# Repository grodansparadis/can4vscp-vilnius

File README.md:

# Vilnius A/D module

This module is part of the [VSCP project](https://www.vscp.org).  It is free to use, modify and sell. The only thing we kindly ask is that improvements and extensions are contributed back to the project (at your will). This to make the project better for everyone. All design files is licensed under the [MIT license](https://en.wikipedia.org/wiki/MIT_License).

## Abstraction

Vilnius A/D module is a CAN4VSCP based module that have four 10-bit A/D channels for 0-5V or 0-10V and also have two 5V I/O channels that can be set as inputs or outputs. General use is to read analog values and as all other VSCP modules you can get the readings reported automatically with a user specified period.

It is also possible to report A/D readings as a VSCP measurement linearized as a floating point value from the formula

measurement = k * A/D-value + m

where k and m are configurable 32-bit floating point constants. You have full control of which event is sent and which unit is used.

This means you can send out any A/D reading as a real unit such as voltage, temperature or in any other SI specified unit.

You can also assign alarm limits so that alarm events are sent when the level goes above a certain value or below a certain value.

Two I/O channels are available. Both can individually be set as inputs or outputs. ON/OFF or TurnOn/TurnOff events can be sent out when I/O change state.

The module can be attached to a standard DIN Rail or be mounted directly on a wall. The mounting enclosures are ordered as separate options when the module is ordered.

The module fully adopts to the VSCP CAN4VSCP specification and can be powered directly over the bus cable with a good 9-28V DC power source. This means there is no need for a separate power cable. VSCP CAN modules are designed to work on a VSCP4CAN bus which use ordinary RJ-45 connectors or use the daisy chain pinhead which can be used to connect modules that are mounted close to each other. For the bus a CAT5 or better twisted pair cable is used. Bus length can have a total length of 500 meters with drops of maximum 24 meters length (up to a total of 120 meters). As for all VSCP4CAN modules the communication speed is fixed at 125 kbps.

All VSCP modules contains information of there own setup, manual, hardware version, manufacturer etc. When VSCP modules are started up they have a default functionality that often is all that is needed to get a working setup. If the module have something to report it will send you an event and if it is setup to react on a certain type of event it will do it's work when you send event(s) to it. It does not need to be harder than that. 

---

## Project files

### User manual
  * [User Manual](https://grodansparadis.github.io/can4vscp-vilnius/#)

### Schematic, PCB, 3D files etc
  * [Schematics reversion B part 1](https://raw.githubusercontent.com/grodansparadis/can4vscp-vilnius/refs/heads/master/eagle/vilnius_sch1_rev_B.png), [part 2](https://raw.githubusercontent.com/grodansparadis/can4vscp-vilnius/refs/heads/master/eagle/vilnius_sch2_rev_B.png)
 * Hardware design files is made in [KiCad](https://kicad.org) and can be found in the `kicad` directory. Valid from reversion B of the hardware.
 * Gerber files for PCB production can be found in the `gerber` directory (in the `kicad` folder).
 * Eagle schema and board files for reversion A and B can be found in the `eagle` directory. They are no longer actively updated.

 ### Firmware

 The firmware is developed in [MPLAB X IDE](https://www.microchip.com/mplab/mplab-x-ide) using the [XC8 compiler](https://www.microchip.com/mplab/compilers).

  * Binary release files is available [here](https://github.com/grodansparadis/can4vscp-vilnius/releases)

### MDF - Module Description File(s)
  * [MDF file version: 10 Release date: 2024-04-25](http://www.eurosource.se/vilnius_1.xml)

### Support
If you need support, please open an issue in the [GitHub repository](https://github.com/grodansparadis/can4vscp-vilnius/issues).

### Buy a ready made modules
You can buy a ready made module from [Grodans Paradis](http://www.grodansparadis.com).

### Project related links
  * [VSCP project](https://www.vscp.org)
  * [VSCP Documentation site](https://docs.vscp.org/)
  * [VSCP Wiki](https://github.com/grodansparadis/vscp/wiki)

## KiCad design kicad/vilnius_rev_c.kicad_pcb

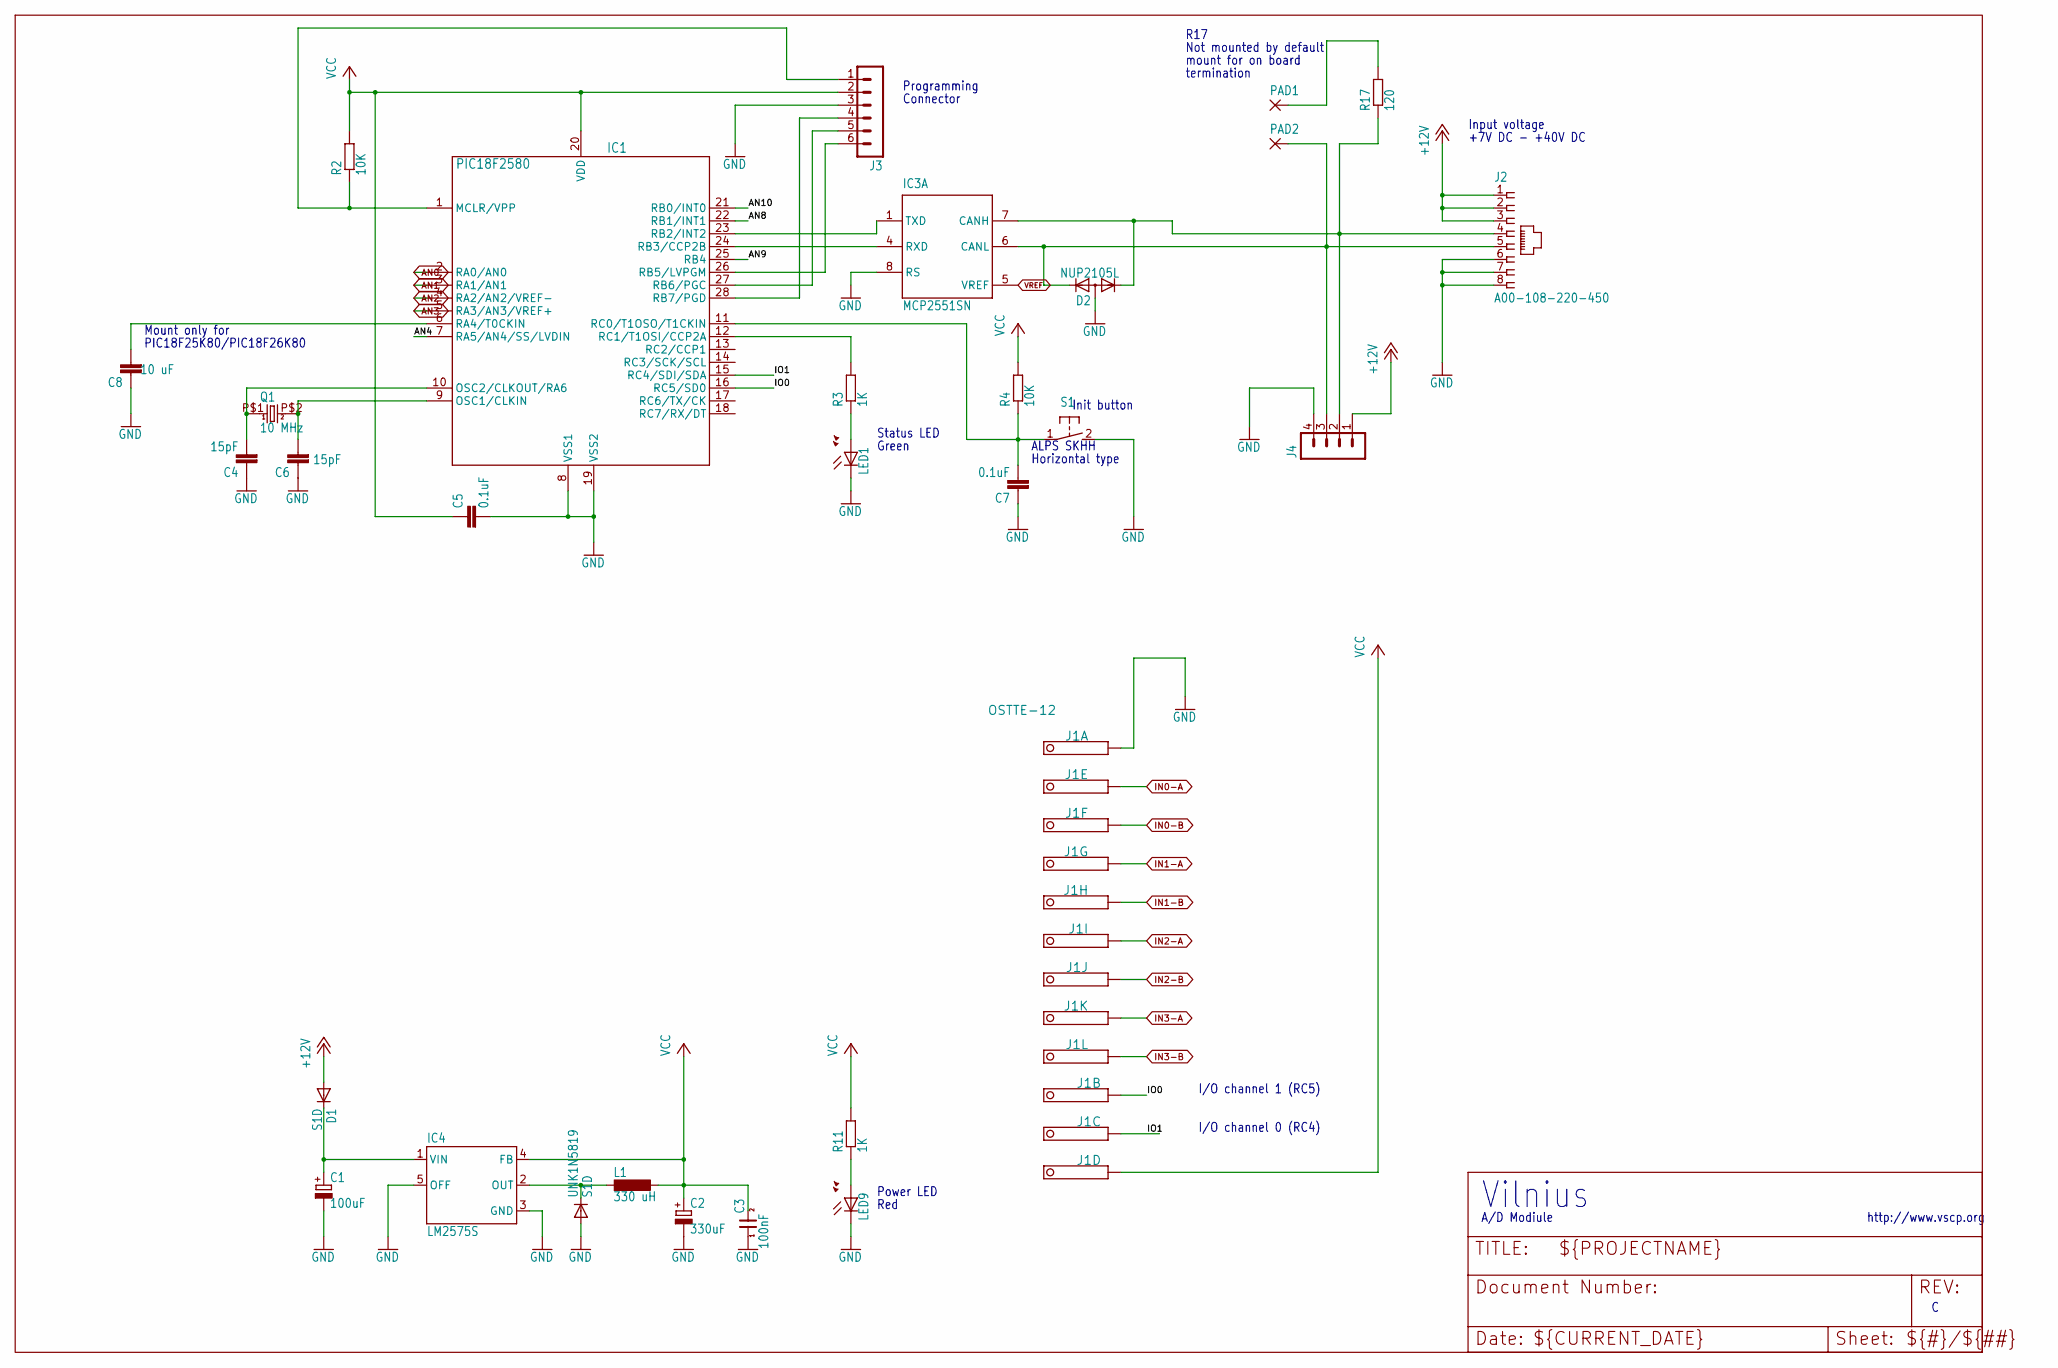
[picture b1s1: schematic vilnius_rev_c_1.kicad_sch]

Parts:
C1: 100uF; PANASONIC_D
C2: 330uF; PANASONIC_D
C3: 100nF; 0805
C4, C6: 15pF; C0805
C5, C7: 0.1uF; C0805
C8: 10 uF; C0805
D1: S1D; SOD123
D2: NUP2105L; SOT23@1
IC1: PIC18F2580; SO28
IC3: MCP2551SN; SO-08
IC4: LM2575S; TO263-5
J1: OSTTE-12; PINHEAD-12
J2: A00-108-220-450; RJ-45
J3: MA06-1
J4: MA04-1
L1: 330 uH; DO3316P
LED1, LED9: LEDCHIP-LED0805; CHIP-LED0805
PAD1, PAD2: 1,6/0,8; 1,6_0,8
Q1: 10 MHz; 9C
R2, R4: 10K; R0805
R3, R11: 1K; R0805
R17: 120; R0805
S1: 31-XX; B3F-31XX
UNK1N5819: S1D; SOD123

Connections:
+12V: D1.A, J2.1, J2.2, J2.3, J4.1
AN0: IC1.2 (RA0/AN0); also elsewhere on the board
AN1: IC1.3 (RA1/AN1); also elsewhere on the board
AN2: IC1.4 (RA2/AN2/VREF-); also elsewhere on the board
AN3: IC1.5 (RA3/AN3/VREF+); also elsewhere on the board
AN4: IC1.7 (RA5/AN4/SS/LVDIN)
AN8: IC1.22 (RB1/INT1)
AN9: IC1.25 (RB4)
AN10: IC1.21 (RB0/INT0)
CANL: D2.2 (K2), IC3.6 (CANL), J2.5, J4.3, PAD2.1
GND: C1.-, C2.-, C3.1, C4.1, C5.2, C6.1, C7.1, C8.1, D2.3 (A), IC1.8 (VSS1), IC1.19 (VSS2), IC3.2 (VSS), IC3.8 (RS), IC4.3 (GND), IC4.5 (OFF), J1.1, J2.6, J2.7, J2.8, J3.3, J4.4, LED1.C, LED9.C, S1.2 (S), UNK1N5819.A; also elsewhere on the board
IN0-A: J1.2; also elsewhere on the board
IN0-B: J1.3; also elsewhere on the board
IN1-A: J1.4; also elsewhere on the board
IN1-B: J1.5; also elsewhere on the board
IN2-A: J1.6; also elsewhere on the board
IN2-B: J1.7; also elsewhere on the board
IN3-A: J1.8; also elsewhere on the board
IN3-B: J1.9; also elsewhere on the board
IO0: IC1.16 (RC5/SD0), J1.10
IO1: IC1.15 (RC4/SDI/SDA), J1.11
unnamed: IC4.2 (OUT), L1.1, UNK1N5819.C
unnamed: C4.2, IC1.10 (OSC2/CLKOUT/RA6), Q1.P$1 (1)
unnamed: C1.+, D1.C, IC4.1 (VIN)
unnamed: IC1.12 (RC1/T1OSI/CCP2A), R3.2
unnamed: LED1.A, R3.1
unnamed: C7.2, IC1.11 (RC0/T1OSO/T1CKIN), R4.1, S1.1
unnamed: C6.2, IC1.9 (OSC1/CLKIN), Q1.P$2 (2)
unnamed: C8.2, IC1.6 (RA4/T0CKIN)
unnamed: PAD1.1, R17.2
unnamed: IC1.1 (MCLR/VPP), J3.1, R2.1
unnamed: IC1.28 (RB7/PGD), J3.4
unnamed: IC1.27 (RB6/PGC), J3.5
unnamed: IC1.26 (RB5/LVPGM), J3.6
unnamed: LED9.A, R11.1
unnamed: D2.1 (K1), IC3.7 (CANH), J2.4, J4.2, R17.1
RXCAN: IC1.24 (RB3/CCP2B), IC3.4 (RXD)
TXCAN: IC1.23 (RB2/INT2), IC3.1 (TXD)
VCC: C2.+, C3.2, C5.1, IC1.20 (VDD), IC3.3 (VDD), IC4.4 (FB), J1.12, J3.2, L1.2, R2.2, R4.2, R11.2; also elsewhere on the board
VREF: IC3.5 (VREF)

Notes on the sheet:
I/O channel 0 (RC4)
Programming
ALPS SKHH
mount for on board
Vilnius
Init button
termination
I/O channel 1 (RC5)
Connector
R17
Not mounted by default
+7V DC - +40V DC
PIC18F25K80/PIC18F26K80
Input voltage
Horizontal type
Status LED
Power LED
Mount only for
A/D Modiule
Red
http://www.vscp.org
Green

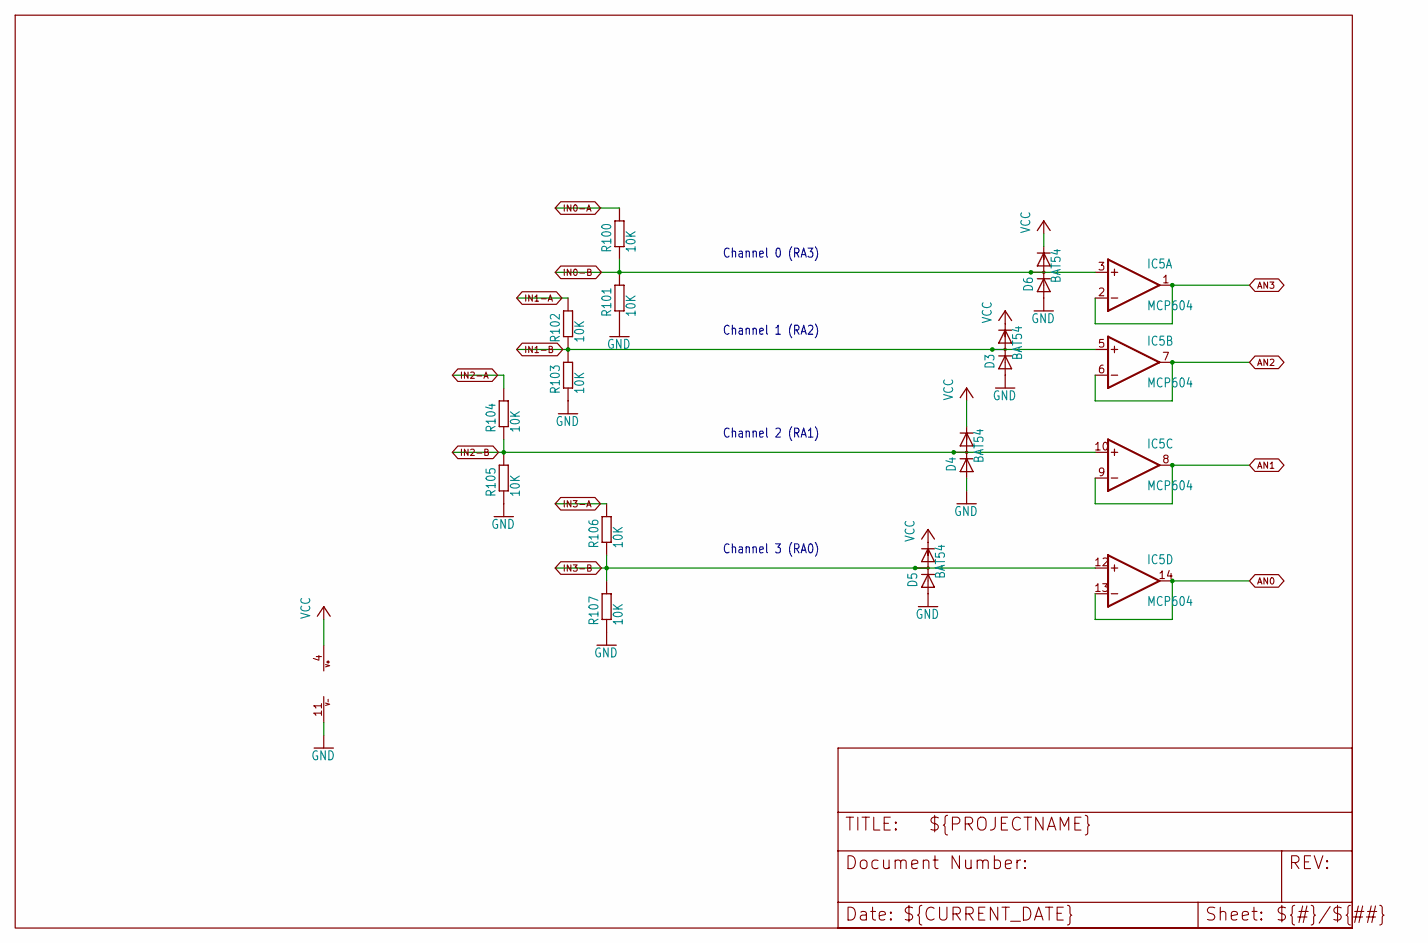
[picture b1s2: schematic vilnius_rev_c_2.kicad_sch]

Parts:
D3, D4, D5, D6: BAT54; SOT23
IC5: MCP604; SO14
R100, R101, R102, R103, R104, R105, R106, R107: 10K; R0805

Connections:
AN0: IC5.13 (-IN), IC5.14 (OUT); also elsewhere on the board
AN1: IC5.8 (OUT), IC5.9 (-IN); also elsewhere on the board
AN2: IC5.6 (-IN), IC5.7 (OUT); also elsewhere on the board
AN3: IC5.1 (OUT), IC5.2 (-IN); also elsewhere on the board
GND: D3.1 (A), D4.1 (A), D5.1 (A), D6.1 (A), IC5.11 (V-), R101.1, R103.1, R105.1, R107.1; also elsewhere on the board
IN0-A: R100.2; also elsewhere on the board
IN0-B: D6.3 (AC), IC5.3 (+IN), R100.1, R101.2; also elsewhere on the board
IN1-A: R102.2; also elsewhere on the board
IN1-B: D3.3 (AC), IC5.5 (+IN), R102.1, R103.2; also elsewhere on the board
IN2-A: R104.2; also elsewhere on the board
IN2-B: D4.3 (AC), IC5.10 (+IN), R104.1, R105.2; also elsewhere on the board
IN3-A: R106.2; also elsewhere on the board
IN3-B: D5.3 (AC), IC5.12 (+IN), R106.1, R107.2; also elsewhere on the board
VCC: D3.2 (C), D4.2 (C), D5.2 (C), D6.2 (C), IC5.4 (V+); also elsewhere on the board

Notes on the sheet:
Channel 3 (RA0)
Channel 0 (RA3)
Channel 1 (RA2)
Channel 2 (RA1)

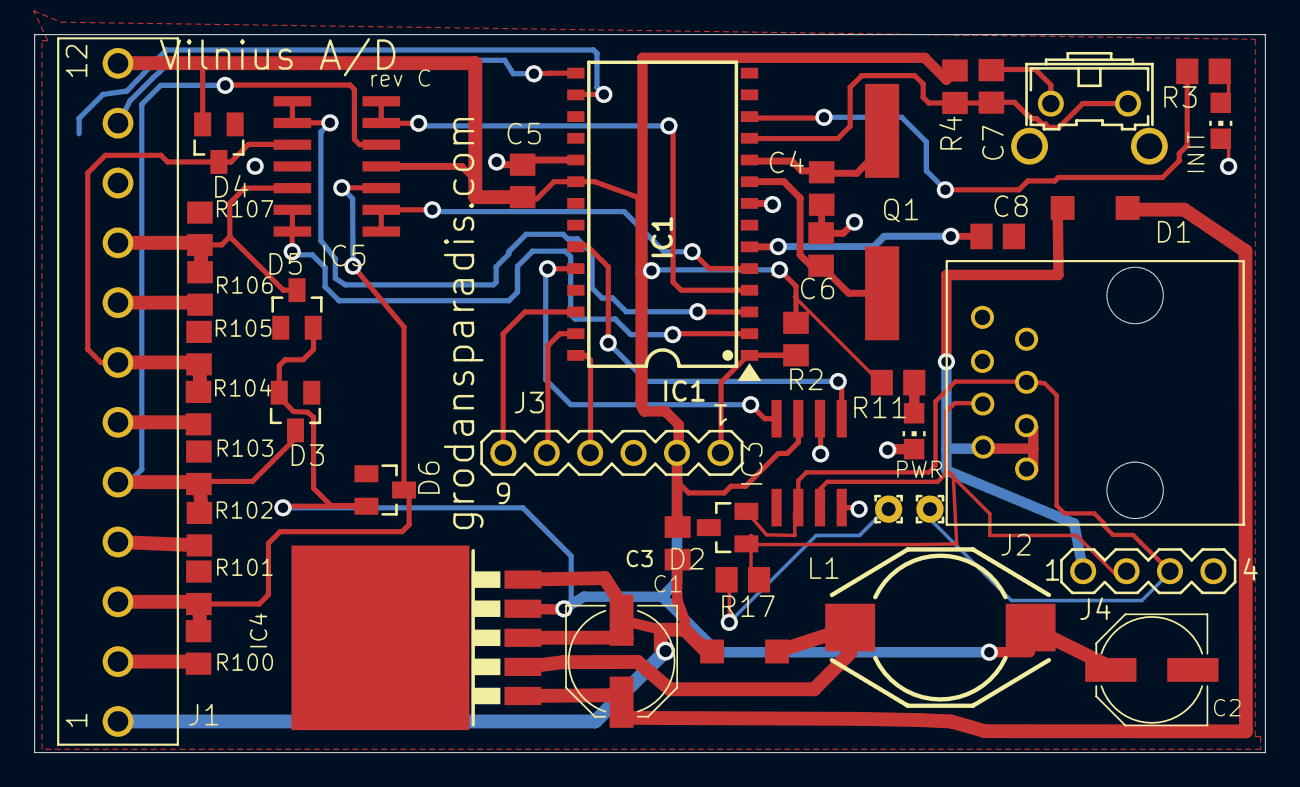
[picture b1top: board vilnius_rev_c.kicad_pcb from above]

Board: 6 copper layers, 72.0 x 42.0 mm, 43 parts (0 on the bottom side), 35 nets.

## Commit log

2025-08-18 Converted schemas to KiCad
2025-09-23 Adopted files to new naming convention
2025-09-30 Changed license to MIT
2025-10-01 Updated readme to have the same info as other can4vscp modules
2025-10-01 Added new manual skeleton
2025-10-01 Added missing nojekyll
2025-10-01 Moved documentation to Markdown
2025-10-01 Cleanup
2025-10-01 Fixed cover page
2026-05-05 Updated license to CERN
